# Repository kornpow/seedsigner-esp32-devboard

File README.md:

# SeedSigner ESP32 Dev-Board
A way to quickly get more developers working on ESP32 code, without having to worry about making it on a breadboard.

# Breadboard Wiring Instructions
The schematic was based on the instructions in this repo

[Keith's wiring instructions](https://github.com/kdmukai/micropython-esp32/tree/main/docs/saola_1r_build)

# Resources
[ESP32 Datasheet](https://www.espressif.com/sites/default/files/documentation/esp32-s2_datasheet_en.pdf)

[Saola User Guide](https://docs.espressif.com/projects/esp-idf/en/latest/esp32s2/hw-reference/esp32s2/user-guide-saola-1-v1.2.html)

[3.3V Regulator Datasheet](http://cn.sg-micro.com/uploads/soft/20220506/1651835177.pdf)

[OV2640 Camera Module](https://www.uctronics.com/download/OV2640_DS.pdf)

[Waveshare 1.3in LCD Hat](https://www.waveshare.com/wiki/1.3inch_LCD_HAT)

# Power Budget
* LDO:      +800mA @ 3.3V
* OV2640:   -60mA  @ 3.3V (max)
* LCD:       -??mA @ 3.3V
* ESP32:    -310mA @ 3.3V (max)

# Pictures

## Schematic

## PCB

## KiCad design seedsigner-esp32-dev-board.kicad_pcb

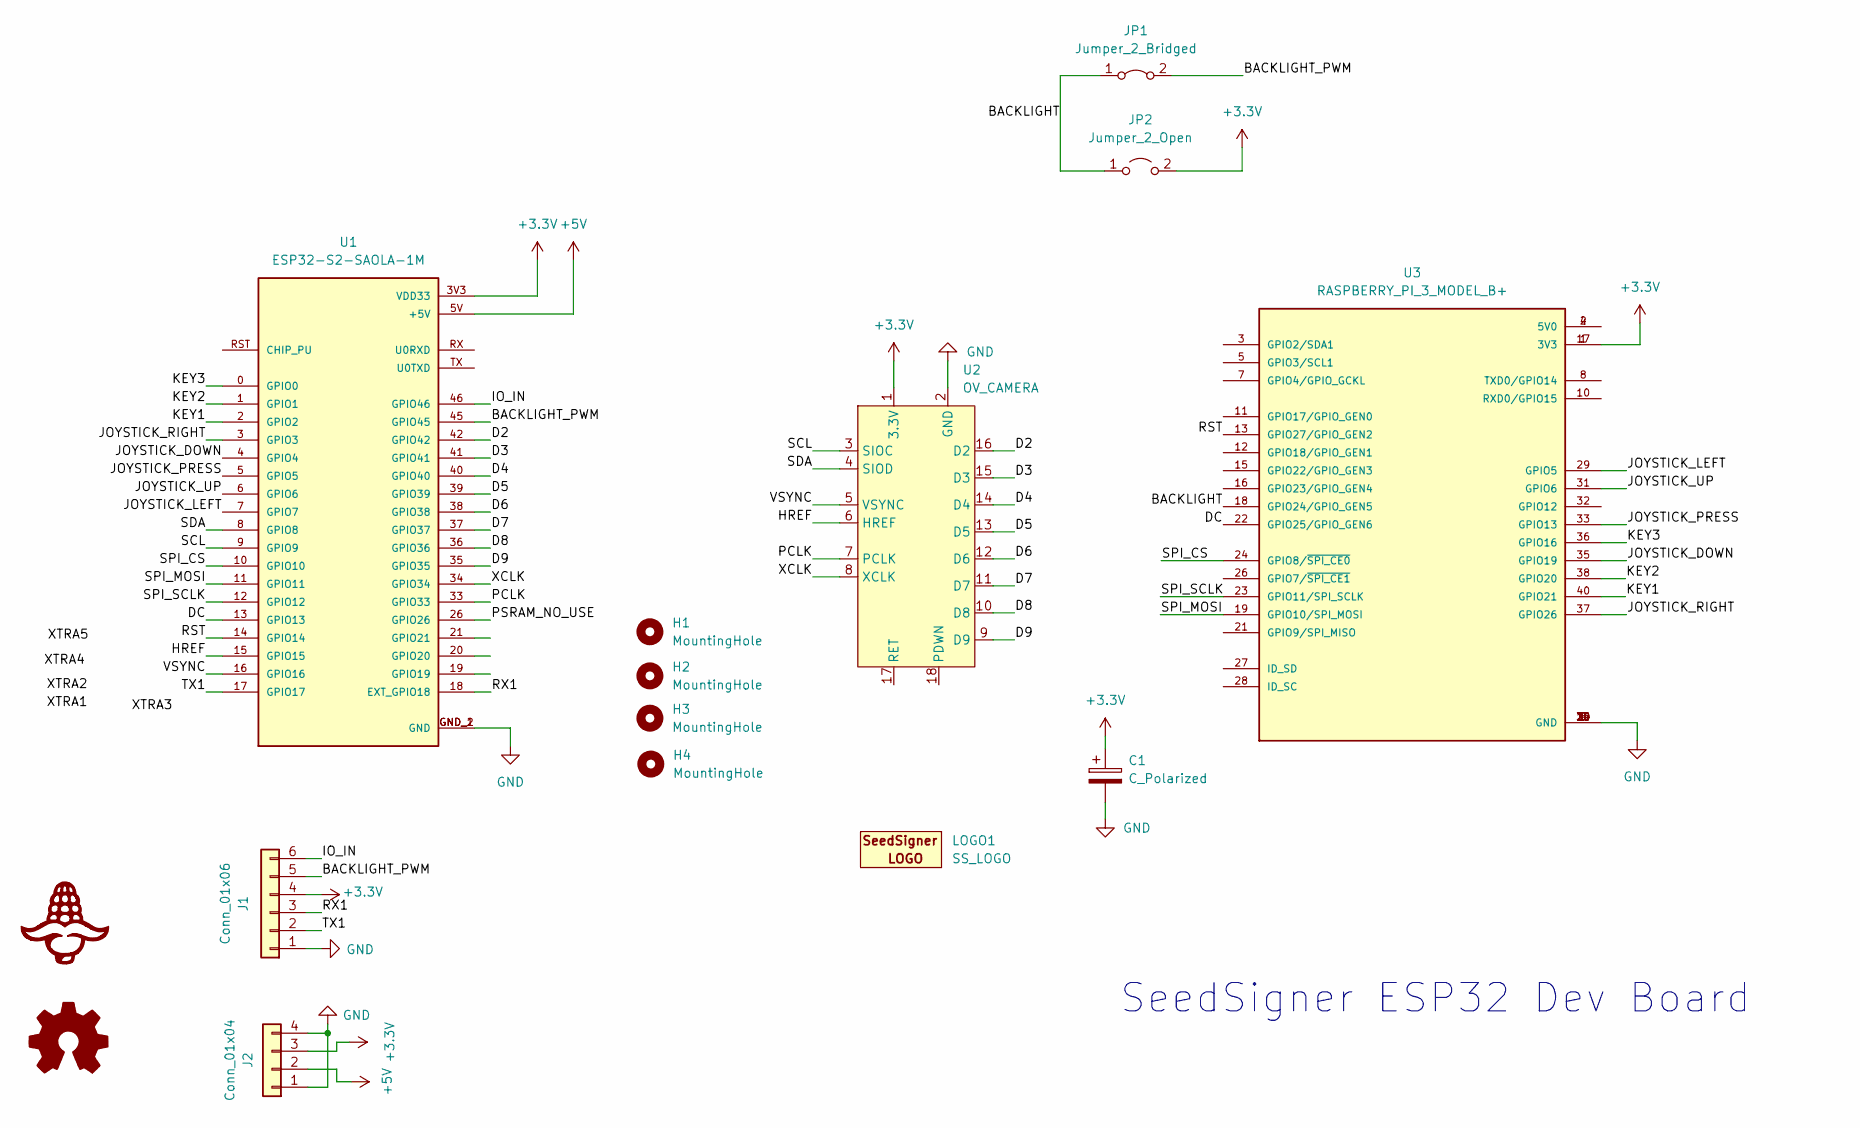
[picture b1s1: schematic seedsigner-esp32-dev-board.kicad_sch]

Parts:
C1: C_Polarized; CP_Radial_D5.0mm_P2.50mm
H1, H2, H3, H4: MountingHole; MOUNT_HOLE_3MM
J1: Conn_01x06; PinHeader_1x06_P2.54mm_Vertical
J2: Conn_01x04; PinHeader_1x04_P2.54mm_Vertical
JP1: Jumper_2_Bridged; SolderJumper-2_P1.3mm_Bridged_Pad1.0x1.5mm
JP2: Jumper_2_Open; SolderJumper-2_P1.3mm_Open_Pad1.0x1.5mm
LOGO1: SS_LOGO; seedsigner-logo-small
LOGO2: CORN-LOGO; corn-logo
U1: ESP32-S2-SAOLA-1M; MODULE_ESP32-S2-SAOLA-1M; PARTREV v1.2
U2: OV_CAMERA; OV_Camera
U3: RASPBERRY_PI_3_MODEL_B+; WAVESHARE_LCD_BUTTON; PARTREV 1.0

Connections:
+3.3V: C1.1, J1.4, J2.3, JP2.2 (B), U1.3V3 (VDD33), U2.1 (3.3V), U3.1 (3V3), U3.17 (3V3)
+5V: J2.2, U1.5V (+5V)
/BACKLIGHT: JP1.1 (A), JP2.1 (A), U3.18 (GPIO24/GPIO_GEN5)
/BACKLIGHT_PWM: J1.5, JP1.2 (B), U1.45 (GPIO45)
/D2: U1.42 (GPIO42), U2.16 (D2)
/D3: U1.41 (GPIO41), U2.15 (D3)
/D4: U1.40 (GPIO40), U2.14 (D4)
/D5: U1.39 (GPIO39), U2.13 (D5)
/D6: U1.38 (GPIO38), U2.12 (D6)
/D7: U1.37 (GPIO37), U2.11 (D7)
/D8: U1.36 (GPIO36), U2.10 (D8)
/D9: U1.35 (GPIO35), U2.9 (D9)
/DC: U1.13 (GPIO13), U3.22 (GPIO25/GPIO_GEN6)
/HREF: U1.15 (GPIO15), U2.6 (HREF)
/IO_IN: J1.6, U1.46 (GPIO46)
/JOYSTICK_DOWN: U1.4 (GPIO4), U3.35 (GPIO19)
/JOYSTICK_LEFT: U1.7 (GPIO7), U3.29 (GPIO5)
/JOYSTICK_PRESS: U1.5 (GPIO5), U3.33 (GPIO13)
/JOYSTICK_RIGHT: U1.3 (GPIO3), U3.37 (GPIO26)
/JOYSTICK_UP: U1.6 (GPIO6), U3.31 (GPIO6)
/KEY1: U1.2 (GPIO2), U3.40 (GPIO21)
/KEY2: U1.1 (GPIO1), U3.38 (GPIO20)
/KEY3: U1.0 (GPIO0), U3.36 (GPIO16)
/PCLK: U1.33 (GPIO33), U2.7 (PCLK)
/PSRAM_NO_USE: U1.26 (GPIO26)
/RST: U1.14 (GPIO14), U3.13 (GPIO27/GPIO_GEN2)
/RX1: J1.3, U1.18 (EXT_GPIO18)
/SCL: U1.9 (GPIO9), U2.3 (SIOC)
/SDA: U1.8 (GPIO8), U2.4 (SIOD)
/SPI_CS: U1.10 (GPIO10), U3.24 (GPIO8/~SPI_CE0)
/SPI_MOSI: U1.11 (GPIO11), U3.19 (GPIO10/SPI_MOSI)
/SPI_SCLK: U1.12 (GPIO12), U3.23 (GPIO11/SPI_SCLK)
/TX1: J1.2, U1.17 (GPIO17)
/VSYNC: U1.16 (GPIO16), U2.5 (VSYNC)
/XCLK: U1.34 (GPIO34), U2.8 (XCLK)
GND: C1.2, J1.1, J2.1, J2.4, U1.GND_1 (GND), U1.GND_2 (GND), U2.2 (GND), U3.6 (GND), U3.9 (GND), U3.14 (GND), U3.20 (GND), U3.25 (GND), U3.30 (GND), U3.34 (GND), U3.39 (GND)
unnamed: U3.2 (5V0), U3.4 (5V0)

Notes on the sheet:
SeedSigner ESP32 Dev Board

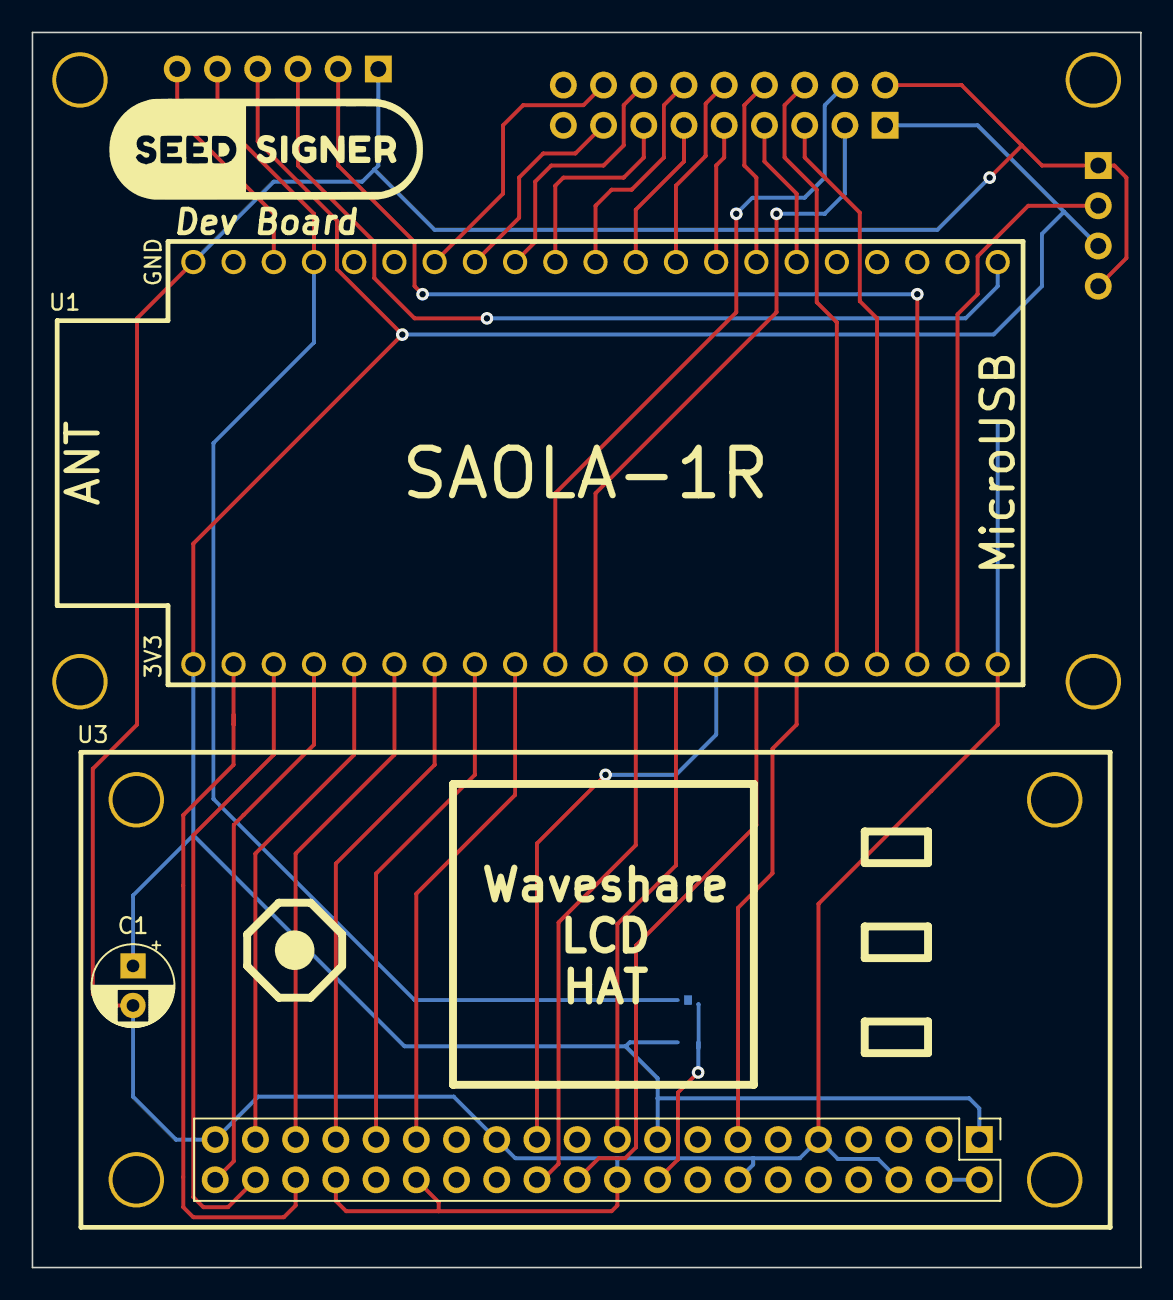
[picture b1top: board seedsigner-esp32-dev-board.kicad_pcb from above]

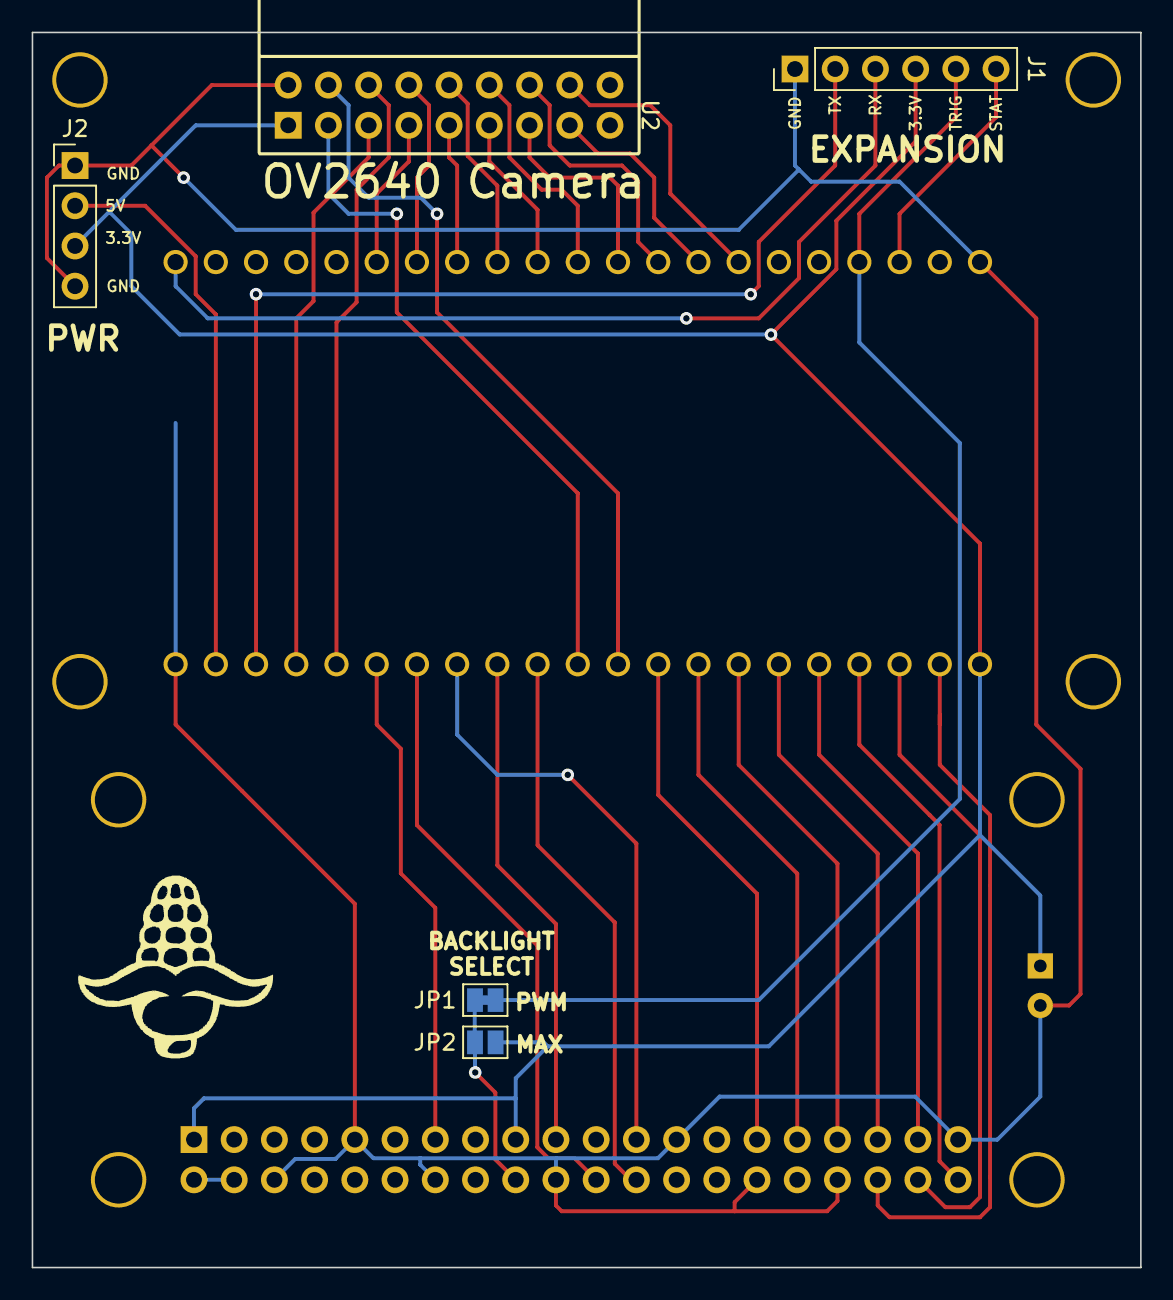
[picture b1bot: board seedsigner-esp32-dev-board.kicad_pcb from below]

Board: 2 copper layers, 70.0 x 78.0 mm, 14 parts (6 on the bottom side), 36 nets.

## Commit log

2022-10-21 initial commit, board is starting to be routed
2022-10-21 add symbol libraries
2022-10-21 libaries are setup properly
2022-10-22 update readme with links, add 3.3v to display and cap
2022-10-22 Add screenshots to readme
2022-10-23 rewire all the pins to make routing cleaner
2022-10-23 fix small wiring issue, add mounting hole for lcd, add silkscreen
2022-10-26 add holes and seedsigner logo
2022-10-27 cleanup and add header for DE2120
2022-10-28 small silkscreen adjustments
2022-10-31 add pinout diagram to readme
2022-11-14 add gerbers and fix RESET and PWM pin
2022-11-14 update README images
2022-11-14 final gerbers and zip
2022-11-18 add bill of materials
